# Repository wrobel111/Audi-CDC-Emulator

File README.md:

# Audi CDC Emulator

Embedded CD changer emulator for Audi factory head units with Bluetooth audio streaming and hands-free phone functionality.

The project emulates an original Audi CD changer, allowing modern Bluetooth connectivity while preserving the original vehicle infotainment system. The hardware and firmware were designed to integrate seamlessly with factory radios without permanent vehicle modifications.

---

## Features

- Audi CD changer (CDC) protocol emulation
- Bluetooth audio streaming (A2DP)
- Hands-free phone functionality (HFP)
- Steering wheel (Rem-C line) and radio button support
- UART communication with Bluetooth module using AT commands
- Custom hardware designed for automotive applications
- AVR firmware written in C/C++

---

## Hardware

### Microcontroller

- ATmega328PB

### Bluetooth module

- BK3254

The Bluetooth module is controlled through UART using AT commands.

Supported AT commands:
https://github.com/tomaskovacik/BK3254/wiki/Supported-commands-and-event-send-from-module

---

## Hardware Design

The PCB was designed specifically for integration with the Audi factory audio system.

Main hardware components include:

- ATmega328PB microcontroller
- BK3254 Bluetooth module
- Audio amplifier
- Automotive power supply interface
- ISP programming connector
- UART service connector

Hardware design files are available in the `Hardware` directory.

---

## Firmware

The firmware is responsible for:

- emulating the Audi CD changer
- controlling the Bluetooth module
- handling button events
- switching between music playback and phone calls
- managing amplifier enable signals
- communication with the factory head unit

- ## Development History

### 24 May 2025

#### Added

- Support for BK3254 Bluetooth module
- Bluetooth music streaming
- Hands-free phone functionality

#### Changed

- Migrated timer implementation from Timer0 to Timer3 on ATmega328PB

---

## PCB Revision Notes (v1.1)

The following improvements are planned for the next PCB revision:

1. Add AUX detection using the switching contacts of the 3.5 mm jack connector.
2. Standardize the design to use the BK3254 Bluetooth module only.
3. Verify amplifier enable signal timing.
4. Replace the programming connector with a standard 6-pin ISP header.
5. Reorder the serial connector pinout:

   - +5 V
   - TX
   - RX
   - GND

6. Replace the audio amplifier with the SSM2211.
   - The SSM2211 uses an active LOW enable input, requiring inverted control logic.
7. Add series resistors and TVS protection diodes on the USB data lines.
8. Improve Digispark module pin placement for easier assembly and debugging.

---

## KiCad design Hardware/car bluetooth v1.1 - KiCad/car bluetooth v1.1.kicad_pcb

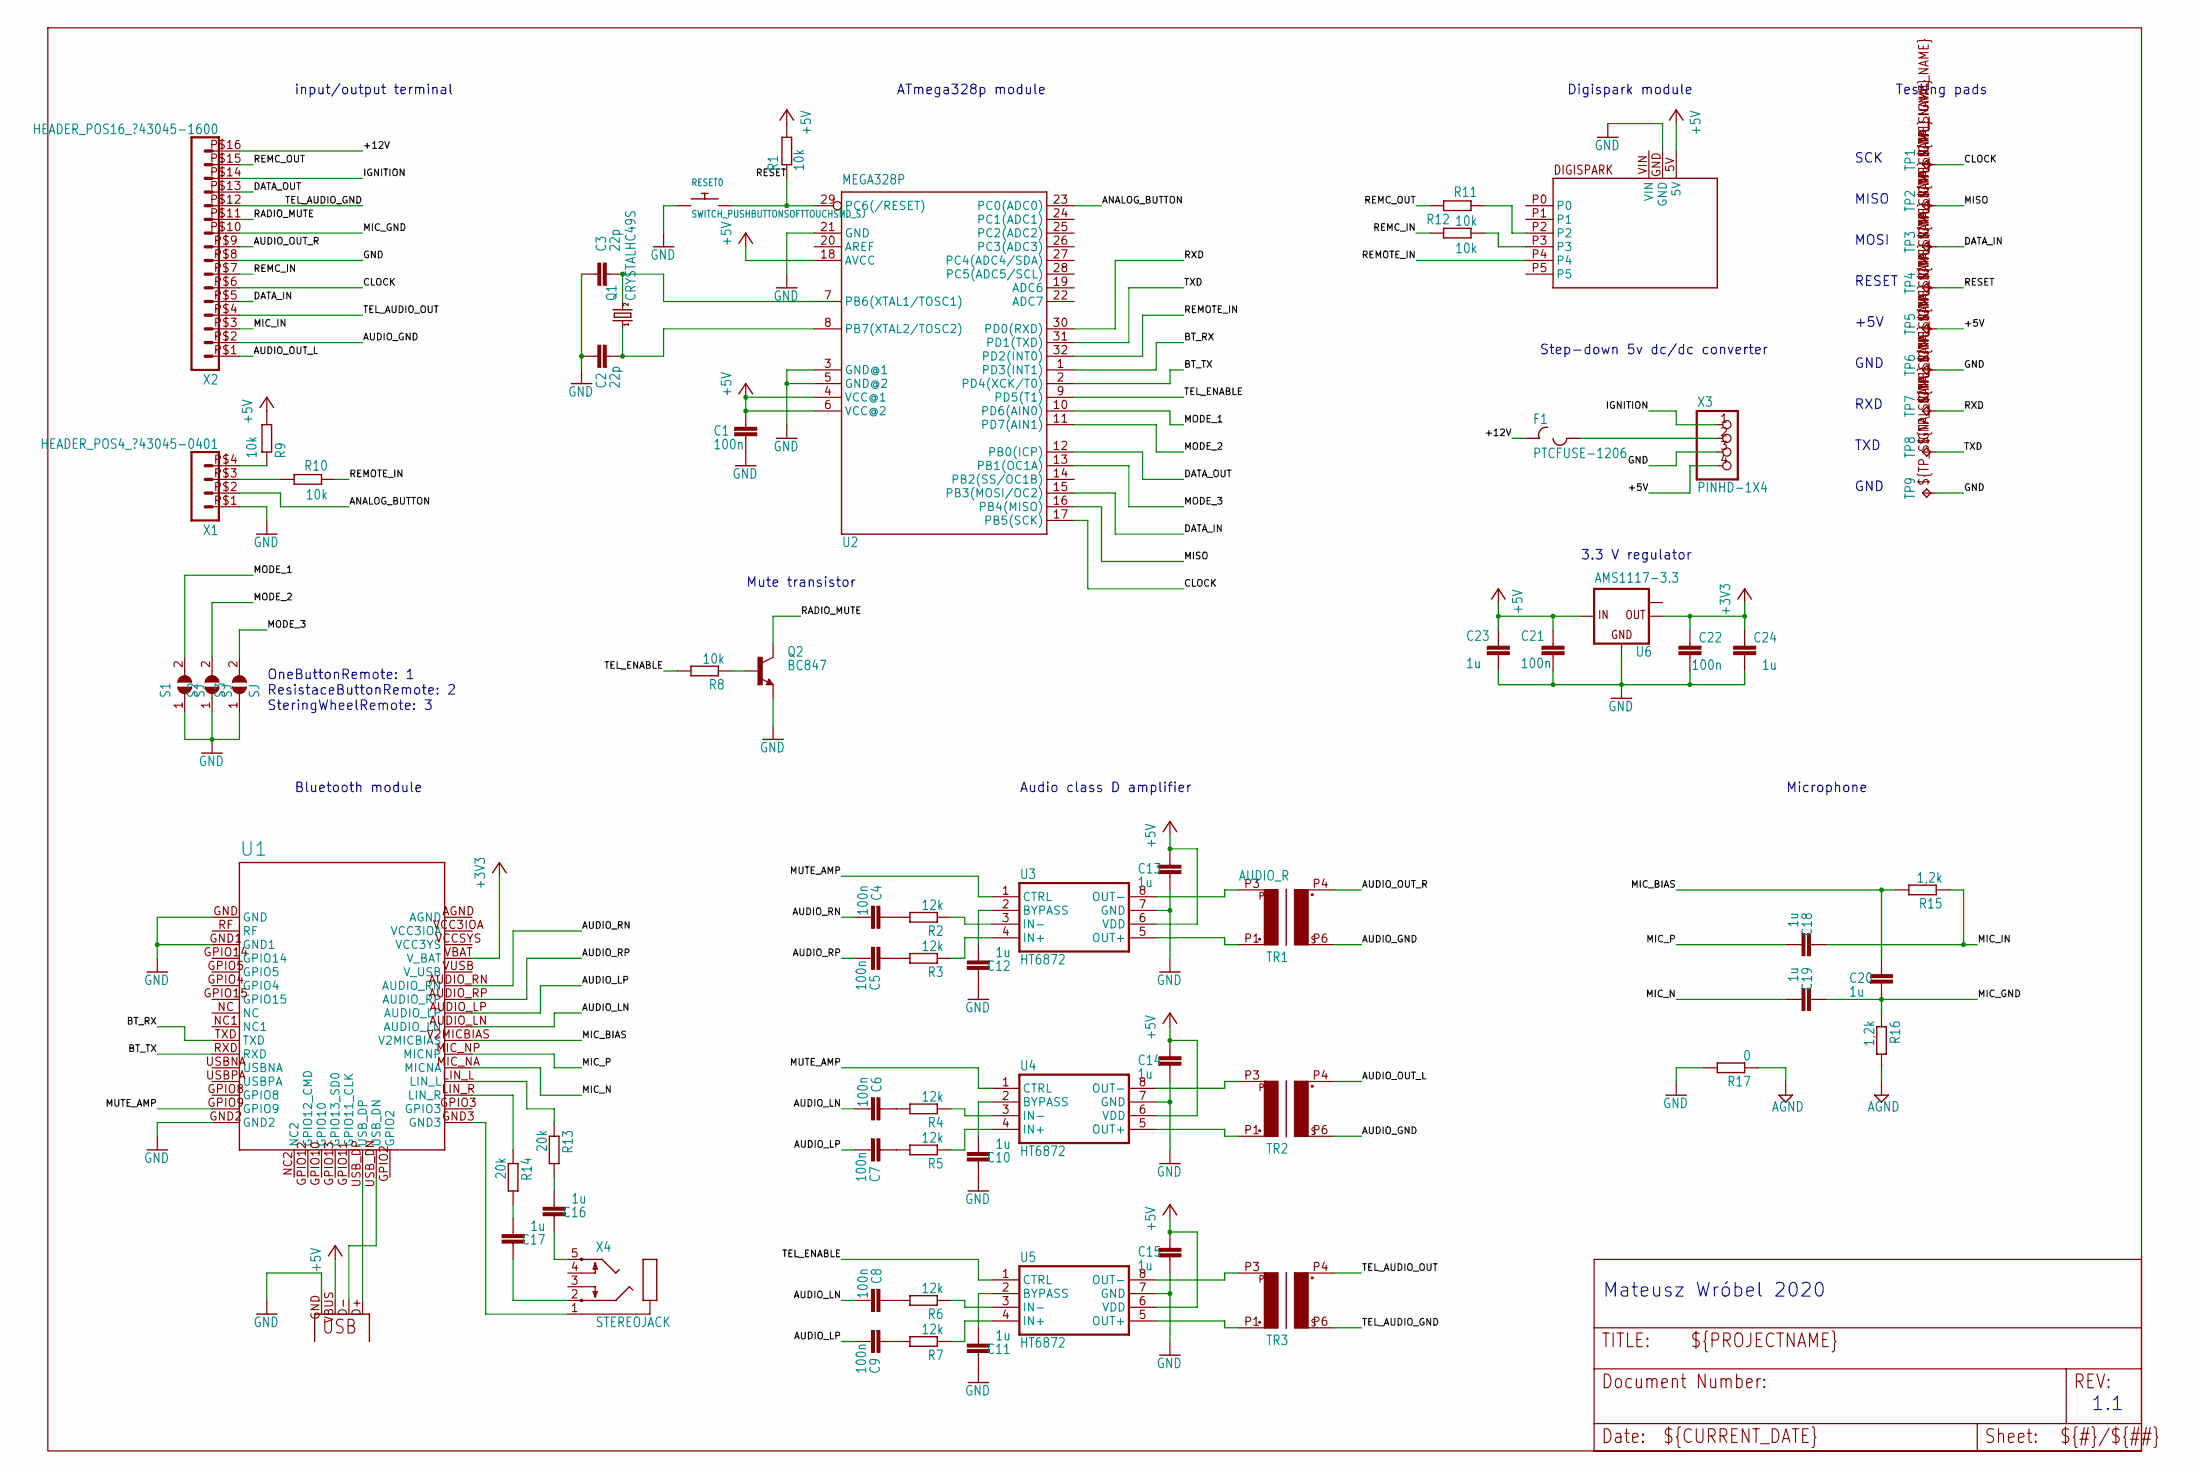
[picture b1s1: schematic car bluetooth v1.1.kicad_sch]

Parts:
C1, C4, C5, C6, C7, C8, C9, C21, C22: 100n; C0805
C2, C3: 22p; C0805
C10, C11, C12, C13, C14, C15, C16, C17, C18, C19, C20, C23, C24: 1u; C0805
F1: PTCFUSE-1206; R1206
Q1: CRYSTALHC49S; HC49_S
Q2: BC847; SOT23
R1, R8, R9, R10, R11, R12: 10k; R0805
R2, R3, R4, R5, R6, R7: 12k; R0805
R13, R14: 20k; R0805
R15, R16: 1,2k; R0805
R17: 0; R0805
RESET0: SWITCH_PUSHBUTTONSOFTTOUCHSMD_SJ; PUSHBUTTON_SMD_SJ
S1, S2, S3: SJ
TP1, TP2, TP3, TP4, TP5, TP6, TP7, TP8, TP9: TPB1,27; B1,27
TR1: AUDIO_R; EI14
TR2: AUDIO_L; EI14
TR3: AUDIO_MIC; EI14
U1: BK3266_BOARD; 40PIN_BOARD
U2: MEGA328P; TQFP32-08
U3, U4, U5: HT6872; SO8
U6: AMS1117-3.3; SOT223
U$7: DIGISPARK
X1: HEADER_POS4_?43045-0401; 43045-0400
X2: HEADER_POS16_?43045-1600; 43045-1600
X3: PINHD-1X4; 1X04
X4: STEREOJACK; STX3100
X5: USB-A-H

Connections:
+3V3: C22.2, C24.2, U1.VBAT (V_BAT), U6.2 (OUT)
+5V: C1.1, C13.1, C14.1, C15.1, C21.1, C23.1, R1.2, R9.1, TP5.TP, U2.4 (VCC@1), U2.6 (VCC@2), U2.18 (AVCC), U3.6 (VDD), U4.6 (VDD), U5.6 (VDD), U6.3 (IN), U$7.5V, X3.4, X5.VBUS
+12V: F1.1, X2.P$16 (16)
AGND: R16.2, R17.1
ANALOG_BUTTON: U2.23 (PC0(ADC0)), X1.P$2 (2)
AUDIO_GND: TR1.P6 (P4), TR2.P6 (P4), X2.P$2 (2)
AUDIO_LN: C6.2, C8.2, U1.AUDIO_LN
AUDIO_LP: C7.2, C9.2, U1.AUDIO_LP
AUDIO_OUT_L: TR2.P4 (P3), X2.P$1 (1)
AUDIO_OUT_R: TR1.P4 (P3), X2.P$9 (9)
AUDIO_RN: C4.2, U1.AUDIO_RN
AUDIO_RP: C5.2, U1.AUDIO_RP
BT_RX: U1.TXD, U2.1 (PD3(INT1))
BT_TX: U1.RXD, U2.2 (PD4(XCK/T0))
CLOCK: TP1.TP, U2.17 (PB5(SCK)), X2.P$6 (6)
DATA_IN: TP3.TP, U2.15 (PB3(MOSI/OC2)), X2.P$5 (5)
DATA_OUT: U2.12 (PB0(ICP)), X2.P$13 (13)
GND: C1.2, C2.1, C3.1, C10.1, C11.1, C12.1, C13.2, C14.2, C15.2, C21.2, C22.1, C23.2, C24.1, Q2.2 (E), R17.2, RESET0.P$1, S1.1, S2.1, S3.1, TP6.TP, TP9.TP, U1.GND, U1.GND1, U1.GND2, U2.3 (GND@1), U2.5 (GND@2), U2.21 (GND), U3.7 (GND), U4.7 (GND), U5.7 (GND), U6.1 (GND), U$7.GND, X1.P$1 (1), X2.P$8 (8), X3.3, X5.GND
IGNITION: X2.P$14 (14), X3.1
MIC_BIAS: C20.1, R15.2, U1.V2MICBIAS
MIC_GND: C19.1, C20.2, R16.1, X2.P$10 (10)
MIC_IN: C18.1, R15.1, X2.P$3 (3)
MIC_N: C19.2, U1.MIC_NA (MICNA)
MIC_P: C18.2, U1.MIC_NP (MICNP)
MISO: TP2.TP, U2.16 (PB4(MISO))
MODE_1: S1.2, U2.10 (PD6(AIN0))
MODE_2: S2.2, U2.11 (PD7(AIN1))
MODE_3: S3.2, U2.13 (PB1(OC1A))
MUTE_AMP: U1.GPIO9, U3.1 (CTRL), U4.1 (CTRL)
unnamed: R14.1, U1.LIN_R
unnamed: C3.2, Q1.2, U2.7 (PB6(XTAL1/TOSC1))
unnamed: C2.2, Q1.1, U2.8 (PB7(XTAL2/TOSC2))
unnamed: Q2.1 (B), R8.1
unnamed: TR2.P3 (P2), U4.8 (OUT-)
unnamed: TR2.P1, U4.5 (OUT+)
unnamed: TR3.P3 (P2), U5.8 (OUT-)
unnamed: TR3.P1, U5.5 (OUT+)
unnamed: TR1.P1, U3.5 (OUT+)
unnamed: R2.1, U3.3 (IN-)
unnamed: R3.1, U3.4 (IN+)
unnamed: R4.1, U4.3 (IN-)
unnamed: R5.1, U4.4 (IN+)
unnamed: R6.1, U5.3 (IN-)
unnamed: R7.1, U5.4 (IN+)
unnamed: C5.1, R3.2
unnamed: C4.1, R2.2
unnamed: C6.1, R4.2
unnamed: C7.1, R5.2
unnamed: C8.1, R6.2
unnamed: C9.1, R7.2
unnamed: R9.2, X1.P$4 (4)
unnamed: R10.1, X1.P$3 (3)
unnamed: R12.2, U$7.P3
unnamed: R11.2, U$7.P2
unnamed: F1.2, X3.2
unnamed: U1.USB_DP, X5.D+
unnamed: C12.2, U3.2 (BYPASS)
unnamed: C10.2, U4.2 (BYPASS)
unnamed: C11.2, U5.2 (BYPASS)
unnamed: U1.USB_DN, X5.D-
unnamed: R13.1, U1.LIN_L
unnamed: TR1.P3 (P2), U3.8 (OUT-)
unnamed: C17.1, X4.2
unnamed: C16.1, X4.5
unnamed: C17.2, R14.2
unnamed: C16.2, R13.2
unnamed: U1.GND3, X4.1
RADIO_MUTE: Q2.3 (C), X2.P$11 (11)
REMC_IN: R12.1, X2.P$7 (7)
REMC_OUT: R11.1, X2.P$15 (15)
REMOTE_IN: R10.2, U2.32 (PD2(INT0)), U$7.P4
RESET: R1.1, RESET0.P$2, TP4.TP, U2.29 (PC6(/RESET))
RXD: TP7.TP, U2.30 (PD0(RXD))
TEL_AUDIO_GND: TR3.P6 (P4), X2.P$12 (12)
TEL_AUDIO_OUT: TR3.P4 (P3), X2.P$4 (4)
TEL_ENABLE: R8.2, U2.9 (PD5(T1)), U5.1 (CTRL)
TXD: TP8.TP, U2.31 (PD1(TXD))

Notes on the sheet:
GND
OneButtonRemote: 1 ResistaceButtonRemote: 2 SteringWheelRemote: 3
Step-down 5v dc/dc converter
Testing pads
RESET
1.1
RXD
3.3 V regulator
Mute transistor
TXD
MISO
MOSI
Microphone
Audio class D amplifier
input/output terminal
+5V
Bluetooth module
ATmega328p module
Digispark module
Mateusz Wróbel 2020
SCK

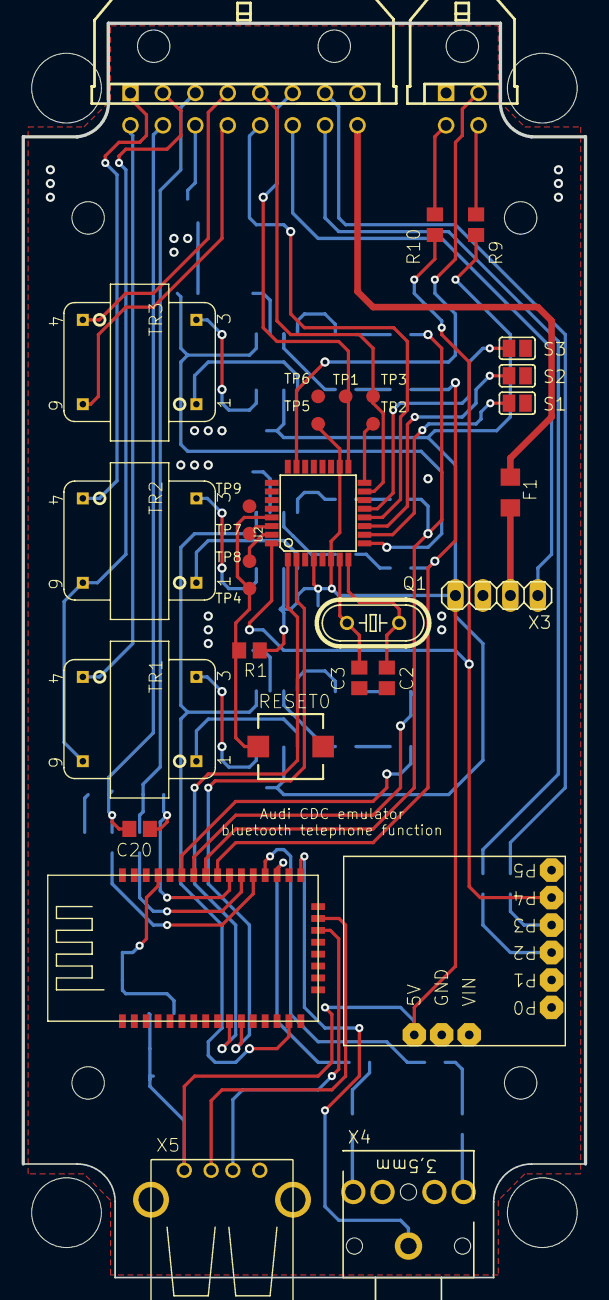
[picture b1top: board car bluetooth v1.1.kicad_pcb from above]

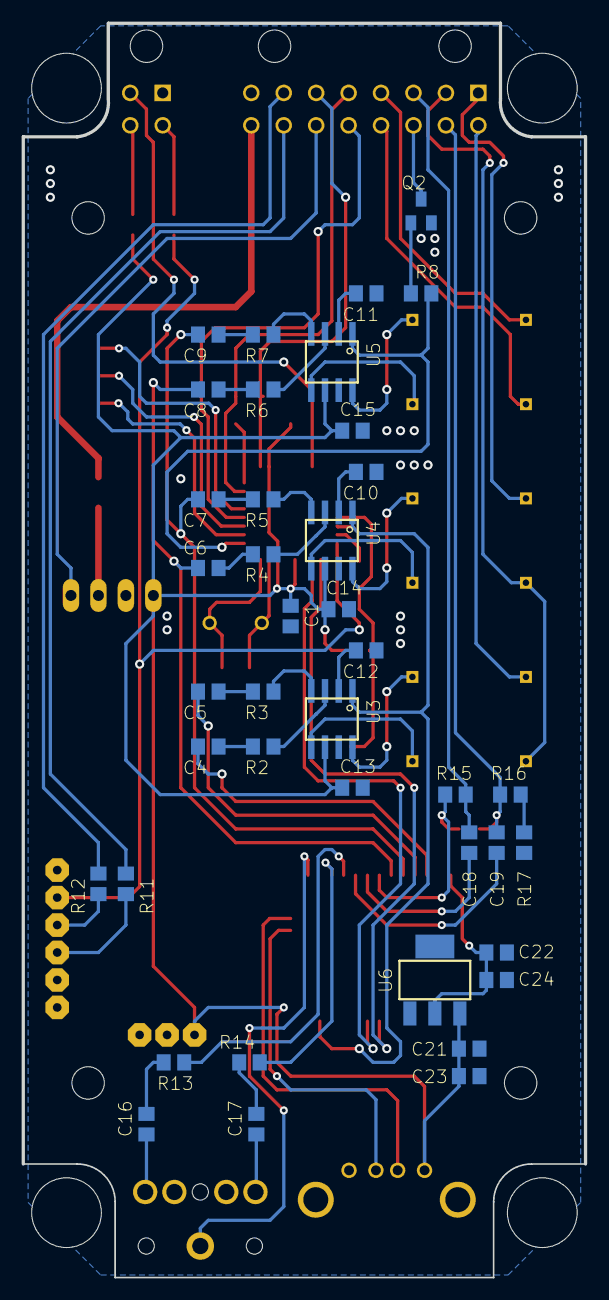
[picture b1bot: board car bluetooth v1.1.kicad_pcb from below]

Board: 16 copper layers, 52.0 x 115.9 mm, 80 parts (40 on the bottom side), 77 nets.

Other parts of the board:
UNK_HOLE_0: dummyfp0
UNK_HOLE_1: dummyfp1
UNK_HOLE_2: dummyfp2
UNK_HOLE_3: dummyfp3
UNK_HOLE_4: dummyfp4
UNK_HOLE_5: dummyfp5
UNK_HOLE_6: dummyfp6
UNK_HOLE_7: dummyfp7

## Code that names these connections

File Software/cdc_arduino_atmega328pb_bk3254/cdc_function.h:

#ifndef VAGRadioRemote_h
#define VAGRadioRemote_h

#include <Arduino.h>
#include <util/delay.h>
#include <avr/io.h>
#include <avr/sfr_defs.h>
#include <stdlib.h>
#include <avr/interrupt.h>
#include <avr/pgmspace.h>

#define OSCILLATOR_8MHz    //comment if oscilator is 16MHz

#define TRUE 1
#define FALSE 0

#define BLUETOOTH

//#define DUMPMODE
//#define DUMPMODE2

// Low period of PWTX line:
// 0: ~650us
// 1: ~1.77ms
// S: ~4.57ms

#if defined(OSCILLATOR_8MHz)
  // if 8MHz timer1 tick is 1µs
  #define STARTTHRESHOLD  3200       // greater than this signifies START bit
  #define HIGHTHRESHOLD   1248       // greater than this signifies 1 bit.
  #define LOWTHRESHOLD     256       // greater than this signifies 0 bit.
  #define PKTSIZE          -32       // command packets are 32 bits long.
#else
  // if 16MHz timer1 tick is 0.5µs
  #define STARTTHRESHOLD  6400       // greater than this signifies START bit
  #define HIGHTHRESHOLD   2496       // greater than this signifies 1 bit.
  #define LOWTHRESHOLD     512       // greater than this signifies 0 bit.
  #define PKTSIZE          -32       // command packets are 32 bits long.
#endif

// do not refresh head unit faster than 5.5ms (currently not implemented)
// 5.24s slow refresh rate when head unit in FM/AM/Tape mode (not implemented)

//#define REFRESH_PERIOD   50       // default to refresh head unit every 50.0ms
#define SECONDWAIT      -20         // wait 20 * 50ms to get 1 second (50ms*20 = 1000ms = 1s)
#define POWERIDENTWAIT  -10         // wait 10 * 1s to 10 seconds between VWCDPICx.x display
#define SCANWAIT        -100        // wait 100 * 50ms to get 5sec (50ms*100 = 5000ms = 5s)
//#define _10MS            156
//#define _50MS            500
//#define _700US            7

#if defined(OSCILLATOR_8MHz)
  #define TIMER0_10MS   78          // 78 × 128 µs = 9.984 ms
  #define TIMER1_
  #define TIMER2_700US  88          // 8 µs x 88 = 704 µs (close enough)  
#else
  #define TIMER0_10MS   156         // 156 × 64 µs = 9.984 ms
  #define TIMER1_
  #define TIMER2_700US  175         // 4 µs x 175 = 700 µs
#endif


#define TX_BUFFER_END   12
#define CAP_BUFFER_END  24

#define VER_MAJOR       '1'
#define VER_MINOR       '0'
#define VER_PATCHLEVEL  'a'

#if defined(__AVR_ATmega88__) || defined(__AVR_ATmega88A__) || defined(__AVR_ATmega328__) || defined(__AVR_ATmega328A__) || defined(__AVR_ATmega328P__) || defined(__AVR_ATmega328PA__) || defined(__AVR_ATmega328PB__)
#define RADIO_COMMAND       PB0 //DATA OUT - from radio to CDC  this pin must be ICP1 !
#define RADIO_COMMAND_DDR   DDRB
#define RADIO_COMMAND_PORT  PORTB
#define RADIO_COMMAND_PIN   PINB
#define RADIO_CLOCK         PD7  //CLOCK
#define RADIO_CLOCK_DDR     DDRD
#define RADIO_CLOCK_PORT    PORTD
#define RADIO_DATA          PB1  //DATA IN - from CDC to radio
#define RADIO_DATA_DDR      DDRB
#define RADIO_DATA_PORT     PORTB
#define RADIO_ACC           3 // PD3 = INT1
#endif



#if defined(__AVR_ATmega324__) || defined(__AVR_ATmega324P__) || defined(__AVR_ATmega324A__) || defined(__AVR_ATmega324PA__) || defined(__AVR_ATmega324PB__)
#define RADIO_COMMAND      PD6 //ICP 
#define RADIO_COMMAND_DDR  DDRD
#define RADIO_COMMAND_PORT  PORTD
#define RADIO_COMMAND_PIN PIND
#define RADIO_CLOCK        PB7
#define RADIO_CLOCK_DDR    DDRB
#define RADIO_CLOCK_PORT  PORTB
#define RADIO_DATA         PB5
#define RADIO_DATA_DDR     DDRB
#define RADIO_DATA_PORT  PORTB
#define RADIO_ACC 3
#endif


// Command Codes
// -------------
//
// First byte is always 53
// Second byte is always 2C
// Third and Fourth bytes always add up to FF
// All command codes seem to be a multiple of 4.
//
//
// 53 2C 0C F3 CD 1
// 53 2C 10 EF DISABLE
// 53 2C 14 EB Change CD (ignored)
// 53 2C 18 E7 Previous CD (only on Audi Concert <)
// 53 2C 2C D3 CD 5 (first packet)
// 53 2C 38 C7 Change CD/Next CD (aka MINQUIRY)
// 53 2C 4C B3 CD 3 (first packet)
// 53 2C 58 A7 Seek Back Pressed
// 53 2C 60 9F Mix 1
// 53 2C 68 97 Up on Mk3 premium (Adam Yellen)
// 53 2C 78 87 Dn
// 53 2C 8C 73 CD 2 (first packet)
// 53 2C A0 5F Scan
// 53 2C A4 5B something to do with power on (Audi Concert)
// 53 2C A8 57 Dn on Mk3 premium (Adam Yellen <adam@yellen.com>)
// 53 2C AC 53 CD 6 (first packet)
// 53 2C CC 33 CD 4 (first packet)
// 53 2C D8 27 Seek Forward Pressed
// 53 2C E0 1F Mix 6
// 53 2C E4 1B ENABLE
// 53 2C F8 07 Up


//#define  Do_PLAY           0x08  // mix button held down (RCD300 head unit only)
#define  Do_PLAY           0x03  // mix button held down (RCD300 head unit only)
#define  Do_LOADCD         0x01  // not used
#define  Do_ENABLE_MK      0x08  // mk concert1
#define  Do_CD1            0x0C  // CD 1
#define  Do_DISABLE        0x10  // DISABLE
#define  Do_CHANGECD       0x14  // Change CD (changer ignores & no ACK)
#define  Do_PREVCD         0x18  // PREVIOUS CD (Audi Concert head unit)
#define  Do_CD5            0x2C  // CD 5
#define  Do_TP             0x30  // TP info (TP button pressed)
#define  Do_SEEKFORWARD_MK 0x38  // mk concert 1 LOAD CD (aka MINQUIRY).
// Also means "Next CD" if no CD button pressed
#define  Do_CD3            0x4C  // CD 3
#define  Do_SEEKBACK       0x58  // SEEK BACK
#define  Do_MIX_CD         0x60  // MIX 1 (mix tracks within one disc)
#define  Do_UP_MK3         0x68  // UP (Mk3 head unit)
#define  Do_DOWN           0x78  // DOWN
#define  Do_CD2            0x8C  // CD 2
#define  Do_SCAN           0xA0  // SCAN
#define  Do_UNKNOWNCMD     0xA4  // power on CD mode?? (Audi Concert head unit)
#define  Do_DOWN_MK3       0xA8  // DOWN (Mk3 head unit only)
#define  Do_CD6            0xAC  // CD 6
#define  Do_CD4            0xCC  // CD 4
#define  Do_SEEKFORWARD    0xD8  // Seek Forward
#define  Do_MIX            0xE0  // MIX 6 (mix tracks across all discs)
#define  Do_ENABLE         0xE4  // ENABLE
#define  Do_UP             0xF8  // UP

#if defined(__AVR_ATmega8__) || defined(__AVR_ATmega128__)
#define TCCR2A TCCR2
#define TCCR2B TCCR2
#define COM2A1 COM21
#define COM2A0 COM20
#define OCR2A OCR2
#define TIMSK2 TIMSK
#define OCIE2A OCIE2
#define TIMER2_COMPA_vect TIMER2_COMP_vect
#define TIMSK1 TIMSK
#define TIFR1 TIFR
#define ICIE1 TICIE1
#define TIMSK0 TIMSK
#define TIFR2 TIFR
#define OCF2A OCF2
#define TCCR0B TCCR0
#endif




void Init_VWCDC(void);  
void OutputPacket(void);
void CDC_Protocol(void);



static void DecodeCommand(void);
static void ScanCommandBytes(void);
static void DumpFullCommand(void);
static uint8_t GetCaptureByte(void);
static void SetStateIdle(void);
static void SetStateTP(void);
static void SetStateIdleThenPlay(void);
static void SetStatePlay(void);
static void SetStateInitPlay(void);
static void SetStatePlayLeadIn(void);
static void SetStateTrackLeadIn(void);
static void SendDisplayBytes(void);
static void SendDisplayBytesNoCD(void);
static void SendDisplayBytesInitCD(void);
static void SendFrameByte(uint8_t byte_u8);
static void SendByte(uint8_t byte_u8);
static void EnqueueString(const uint8_t *addr PROGMEM);
static void EnqueueHex(uint8_t hexbyte_u8);
static void ResetTime(void);
static void SendStateIdle(void);
static void SendStateTP(void);
static void SendStatePlayLeadInEnd(void);
static void SendStateInitPlayEnd(void);
static void SendStateInitPlayAnnounceCD(void);
static void SendStatePlayLeadInAnnounceCD(void);
static void SendPacket(void);
static void android_buttons();
static void printstr_p(const char *s);
static uint8_t cdButtonPushed(uint8_t cdnumber);

#endif

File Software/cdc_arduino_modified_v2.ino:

/*****************************************************************************


   Audi/Volkswagen Audi Interface
   
   Target: arduino atmega328(tested)


   Orginal Author: Vincent

   Date: January, 2011

   Version: 0.01


   Originally ported from VWCDPIC Project:

   http://www.k9spud.com/vwcdpic/

   Ported from Matthias Koelling's AVR Code:

   www.mikrocontroller.net/attachment/31279/vwcdc.c

   ---------------------------------
   16. Mar 2015:

   https://github.com/tomaskovacik/
   arduino duemilanove works:

   RADIO PIN -> arduino pin

   DataOut   -> digital 8 (ICP1)
   DataIn    -> digital 11(PB3)
   Clock     -> digital 13(PB5)

   computer -> arduino pin
   serial TX -> digital 0 (PD0)
   serial RX -> digital 1 (PD1)

   19. Mar 2015  tomaskovacik
   port to atmega8

   14.Jun 2019 kovo
   this compile fine against mega324(P/A/PA/PB)
   
   ---------------------------------
   Mateusz Wrobel 27. Sep 2020
   - bluetooth BK3266 module 
   - telephone comunication (music and calling)


 *****************************************************************************/
#include "bk3266.h"
#include "cdc_function.h"
#include "Remote.h"
#include <SoftwareSerial.h>

int main()
{
  Serial.begin(9600);
  
  Init_VWCDC();
  InitRemote();
  InitBK3266();

  while (1)
  {
    #ifdef CHIP_BK3266
        CheckStateBK3266();
    #endif
    #ifdef CHIP_BK3254
       CheckStateBK3254();
    #endif
    
    CDC_Protocol();
    RemoteProtocol();
  } 
}

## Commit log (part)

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2021-02-03 start repo
2023-01-02 Zmiany w plikach
    utworzenie klas, przebudowanie funkcji remote, nowa biblioteka do bk3265
2023-01-29 Porządki w kodzie
    utworzone klasy
